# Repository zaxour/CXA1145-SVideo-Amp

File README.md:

# CXA1145-SVideo-Amp
S-Video amp for CXA1145 encoders, based on the circuit used in the Amiga CD32. Connect Y (Luma) to pin 16, C (Chroma) to pin 15. 

This has been tested with a Model 1 Sega Genesis using the CXA1145P. Screenshots taken from a Model 1 VA6 Genesis, with RGB bypassed with 4BP, via Retrotink 5X.

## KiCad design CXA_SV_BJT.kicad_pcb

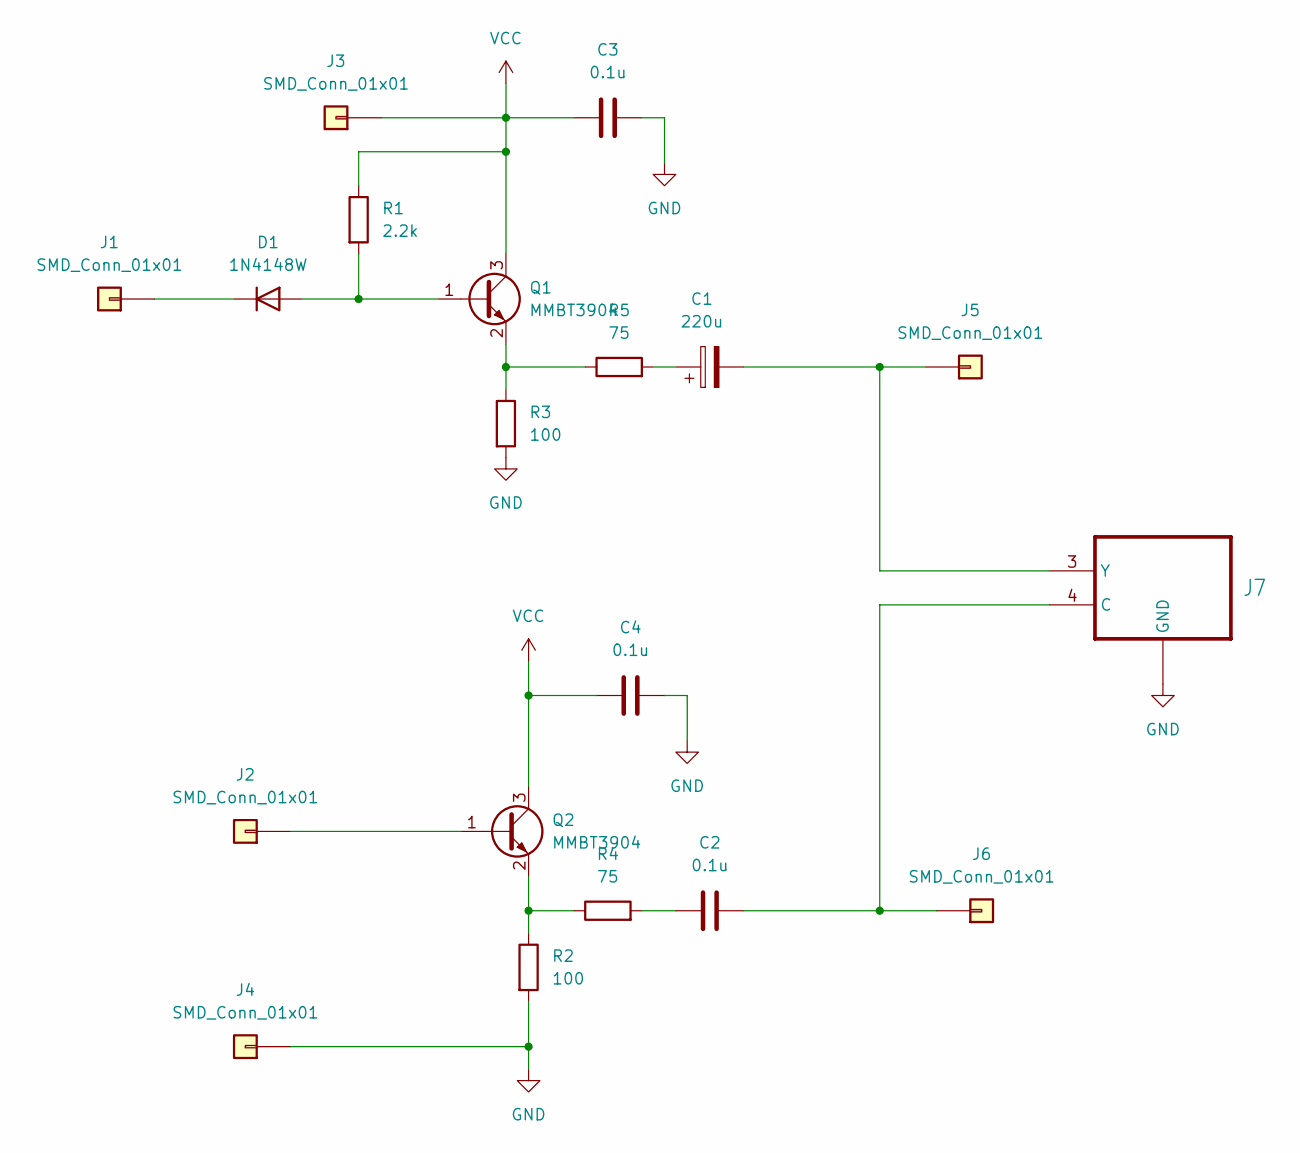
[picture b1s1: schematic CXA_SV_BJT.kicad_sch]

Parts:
C1: 220u; CP_EIA-3528-15_AVX-H
C2, C3, C4: 0.1u; C_0603_1608Metric
D1: 1N4148W; D_SOD-123
J1, J2, J3, J4, J5, J6: SMD_Conn_01x01; SolderWirePad_1x01_SMD_1x2mm
J7: MD40S_SVid; CUI_MD-40SM
Q1, Q2: MMBT3904; SOT-23
R1: 2.2k; R_0603_1608Metric
R2, R3: 100; R_0603_1608Metric
R4, R5: 75; R_0603_1608Metric

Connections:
GND: C3.2, C4.2, J4.1, J7.1 (GND), J7.2 (GND), J7.S1 (GND), J7.S2 (GND), J7.S3 (GND), R2.2, R3.2
unnamed: C1.1, R5.2
unnamed: C2.1, R4.2
unnamed: D1.2 (A), Q1.1 (B), R1.2
unnamed: D1.1 (K), J1.1
unnamed: J2.1, Q2.1 (B)
unnamed: C1.2, J5.1, J7.3 (Y)
unnamed: C2.2, J6.1, J7.4 (C)
unnamed: Q1.2 (E), R3.1, R5.1
unnamed: Q2.2 (E), R2.1, R4.1
VCC: C3.1, C4.1, J3.1, Q1.3 (C), Q2.3 (C), R1.1

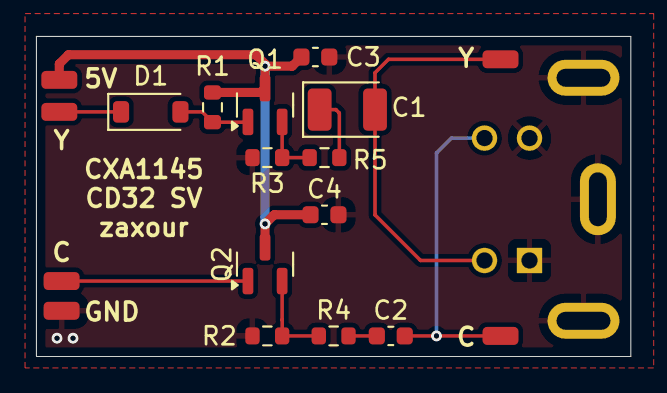
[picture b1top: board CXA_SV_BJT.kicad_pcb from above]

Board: 2 copper layers, 33.0 x 17.8 mm, 19 parts (1 on the bottom side), 11 nets.
